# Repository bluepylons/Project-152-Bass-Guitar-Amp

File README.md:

This is a preamplifier circuit for a bass-amp, using much of [Rod Elliot's design](https://sound-au.com/project152-1.htm) over at Sound Au, with some changes:

* The EQ board is broken off into a separate board, so that the main preamp design could be used with different EQ schemes (graphic, etc.). 
* I skipped adding a compressor, though this can probably be added immediately after the EQ chain if needed.
* Added a headphone output

Since Chinese PCB fabrication is dramatically cheaper if your design is 100x100mm or smaller, this design is broken up into separate boards for the preamp, linear power supply (+/-12V), and EQ stages.

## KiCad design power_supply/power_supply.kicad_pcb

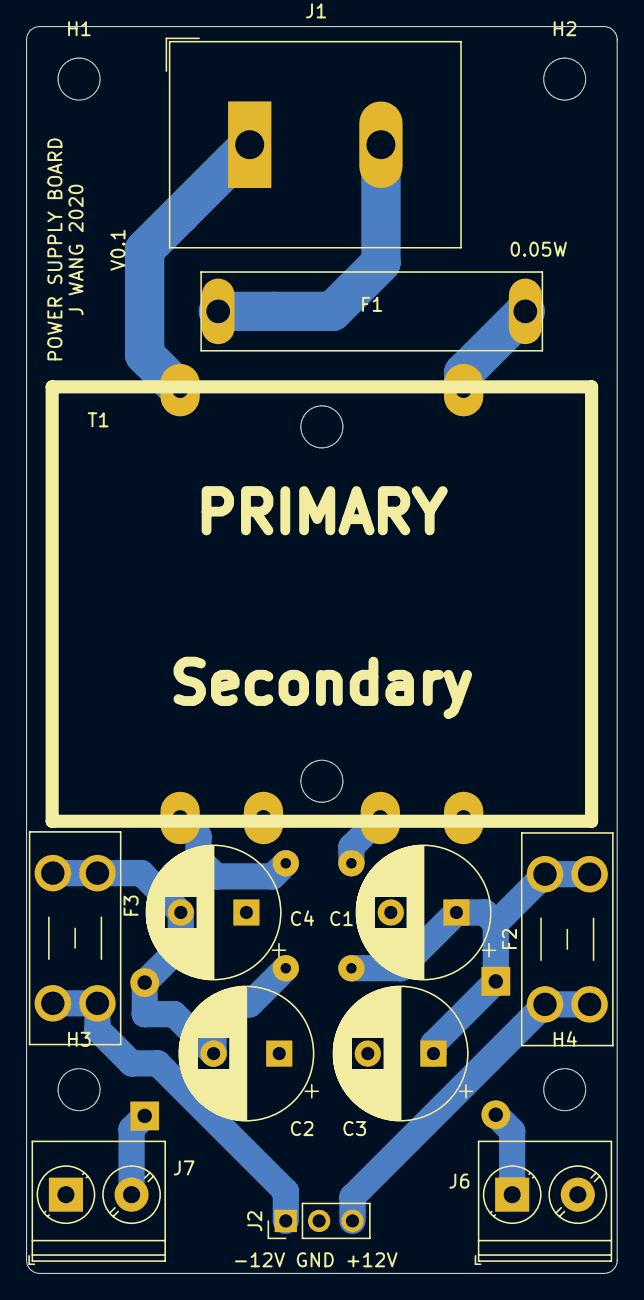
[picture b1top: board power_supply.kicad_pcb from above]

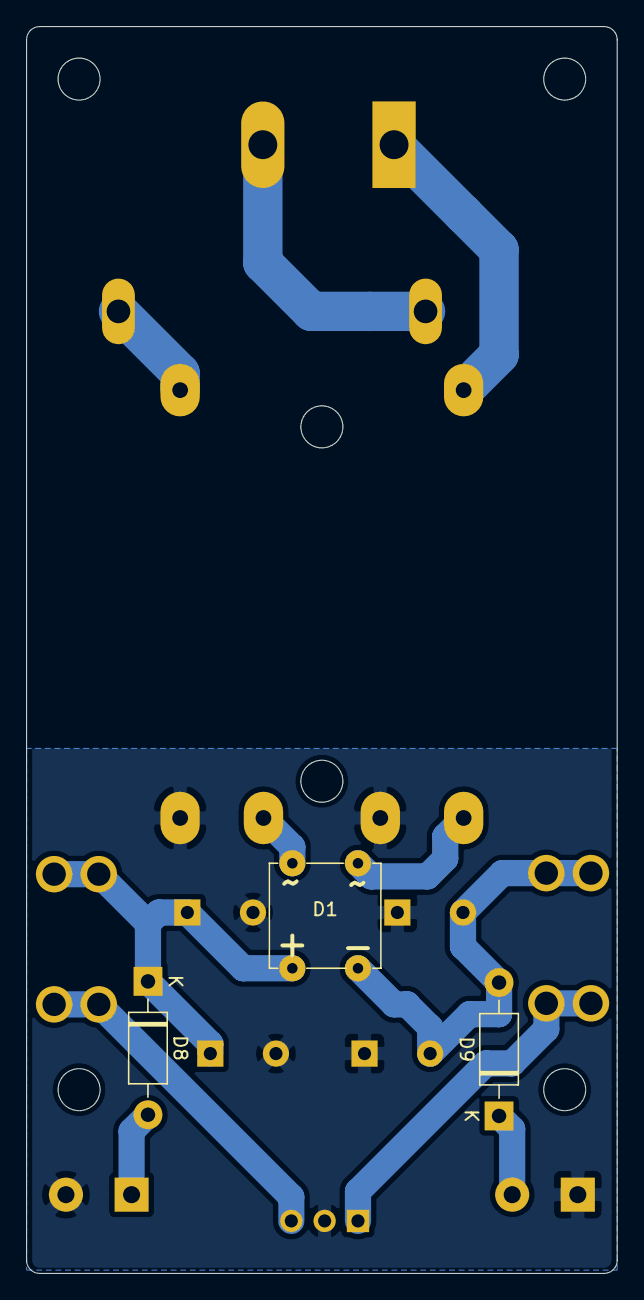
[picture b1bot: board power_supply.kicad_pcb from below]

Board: 2 copper layers, 45.0 x 95.0 mm, 19 parts (3 on the bottom side), 12 nets.

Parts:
C1, C2, C3, C4: 1000uF 35V; CP_Radial_D10.0mm_P5.00mm
D1: D_Bridge_+-AA; DiodesIncDF-M
D8, D9: 1N5819; D_DO-41_SOD81_P10.16mm_Horizontal
F1: Fuse; Keystone-3527-Fuseholder
F2, F3: Fuse; Fuseholder_Blade_Mini_Keystone_3568
H1, H2, H3, H4: MountingHole; MountingHole_3.2mm_M3_DIN965
J1: Conn_01x02_Female; TerminalBlock_Dinkle_DT-55-B01X-02_P10.00mm
J2: Conn_01x03_Male; PinHeader_1x03_P2.54mm_Vertical
J6, J7: Conn_01x02_Male; TerminalBlock_Phoenix_PT-1,5-2-5.0-H_1x02_P5.00mm_Horizontal
T1: Transformer_1P_2S; TE490080XXRC62

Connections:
+12V: C1.1, C3.1, D1.1, D8.1, F2.2
-12V: C2.2, C4.2, D1.2, D9.2, F3.2
GND: C1.2, C2.1, C3.2, C4.1, J2.2, J6.2, J7.1, T1.4, T1.5
unnamed: D1.3, T1.6
unnamed: D1.4, T1.3
unnamed: D8.2, J6.1
unnamed: D9.1, J7.2
unnamed: F1.1, T1.1
unnamed: F1.2, J1.2
unnamed: F2.1, J2.3
unnamed: F3.1, J2.1
unnamed: J1.1, T1.2

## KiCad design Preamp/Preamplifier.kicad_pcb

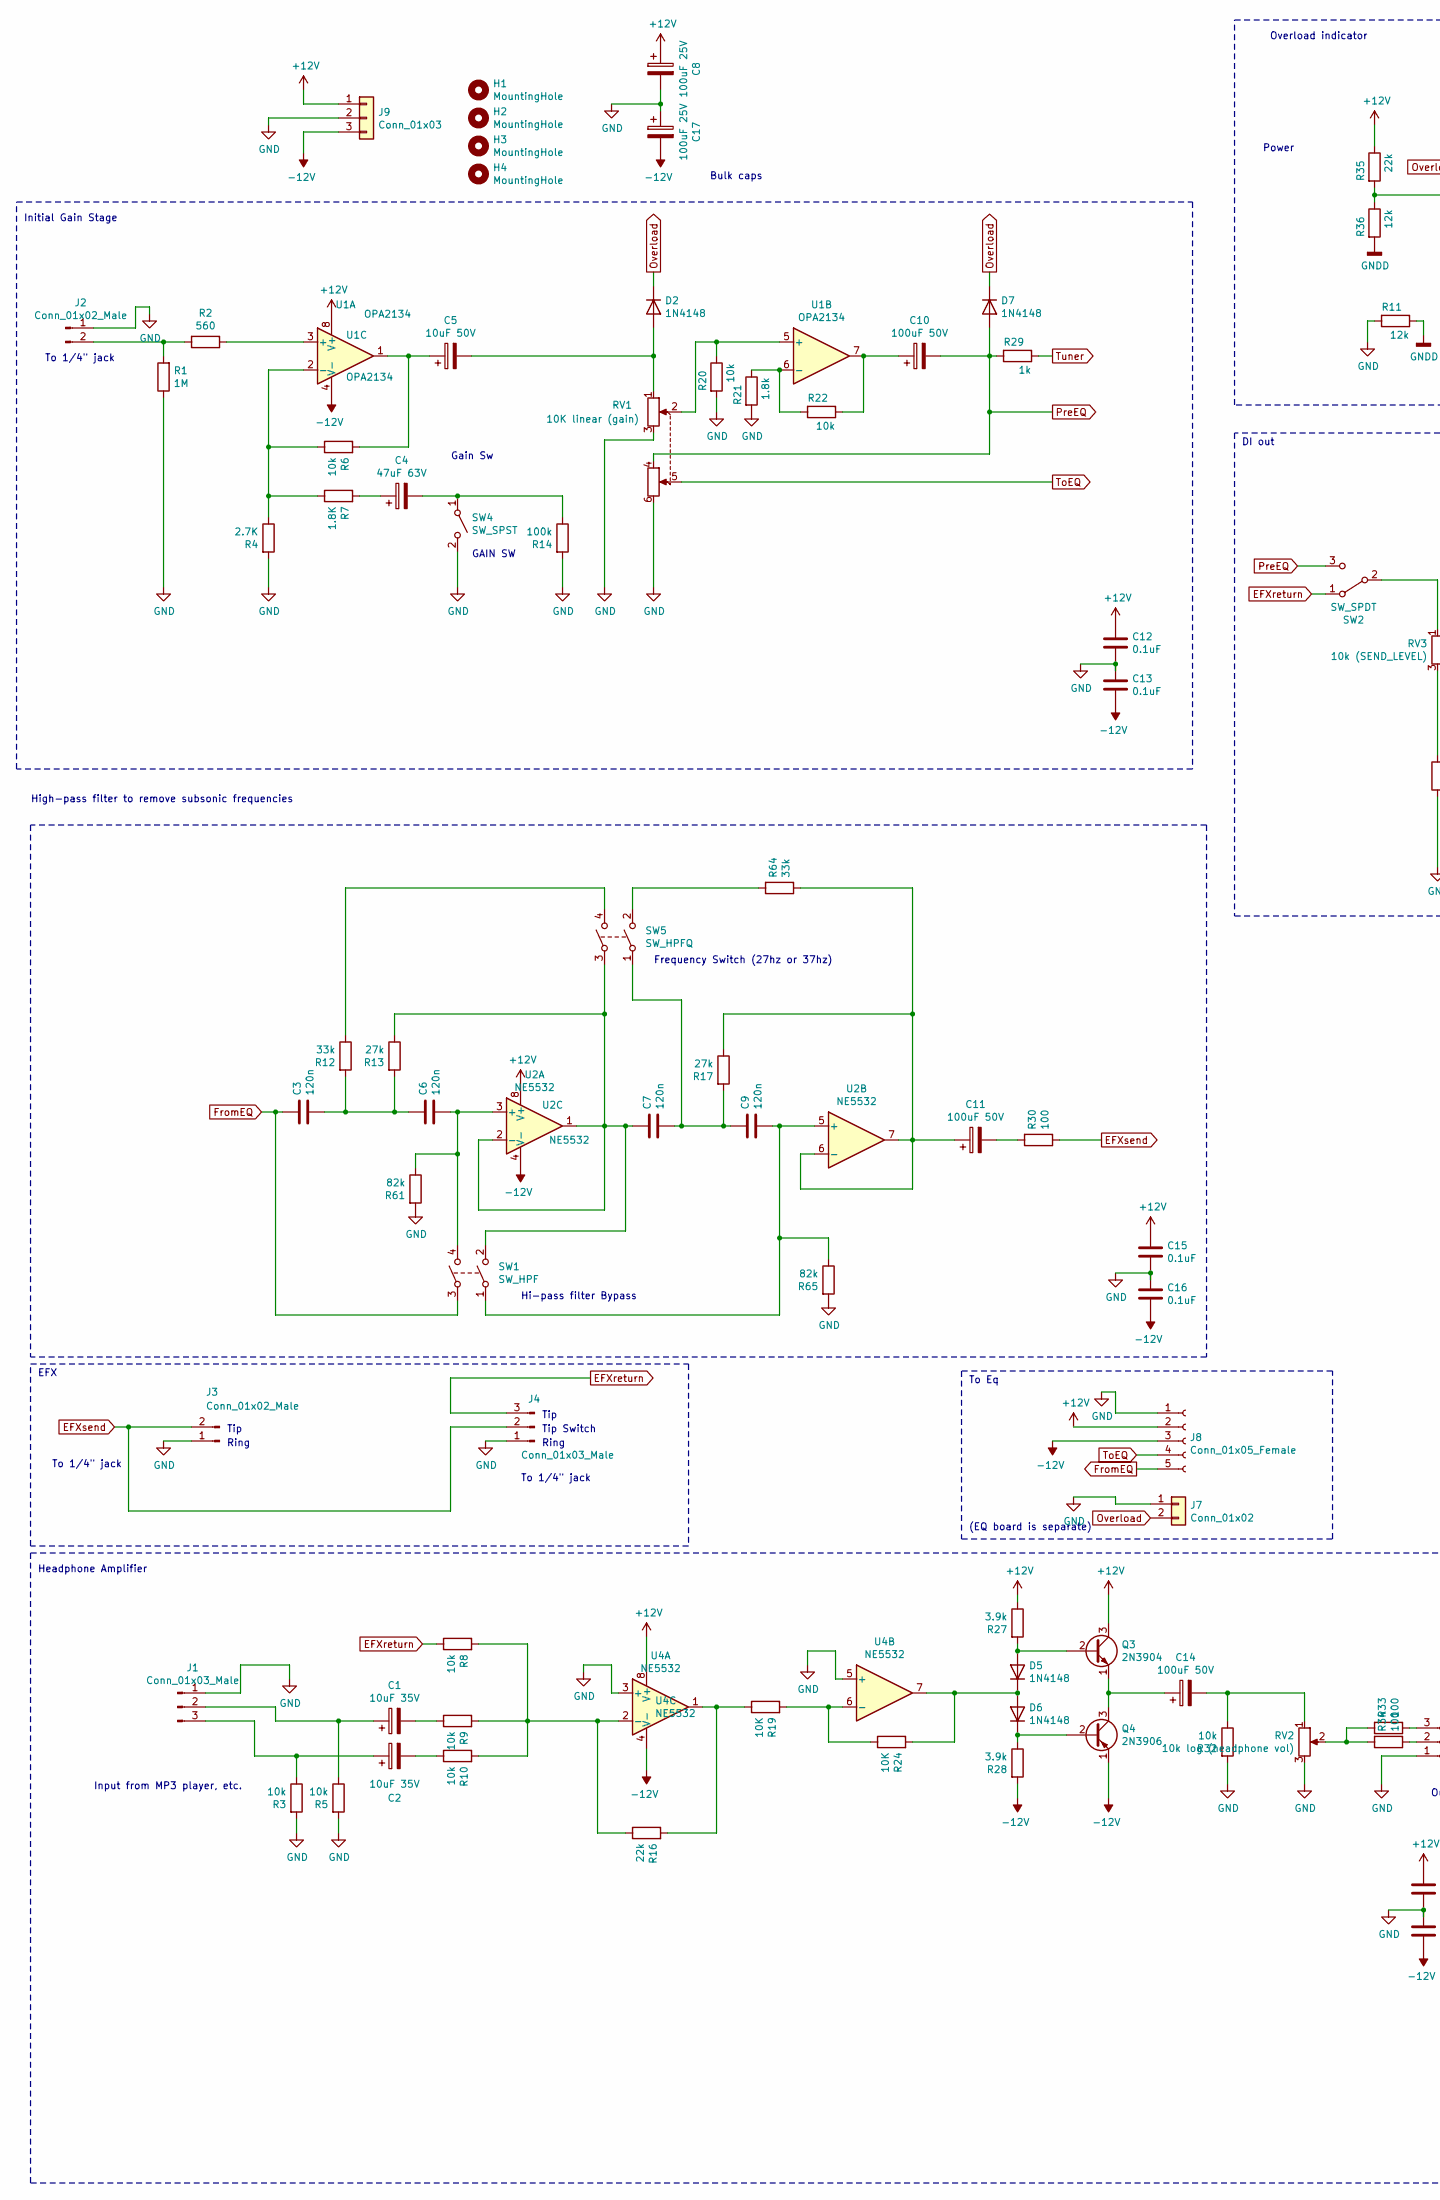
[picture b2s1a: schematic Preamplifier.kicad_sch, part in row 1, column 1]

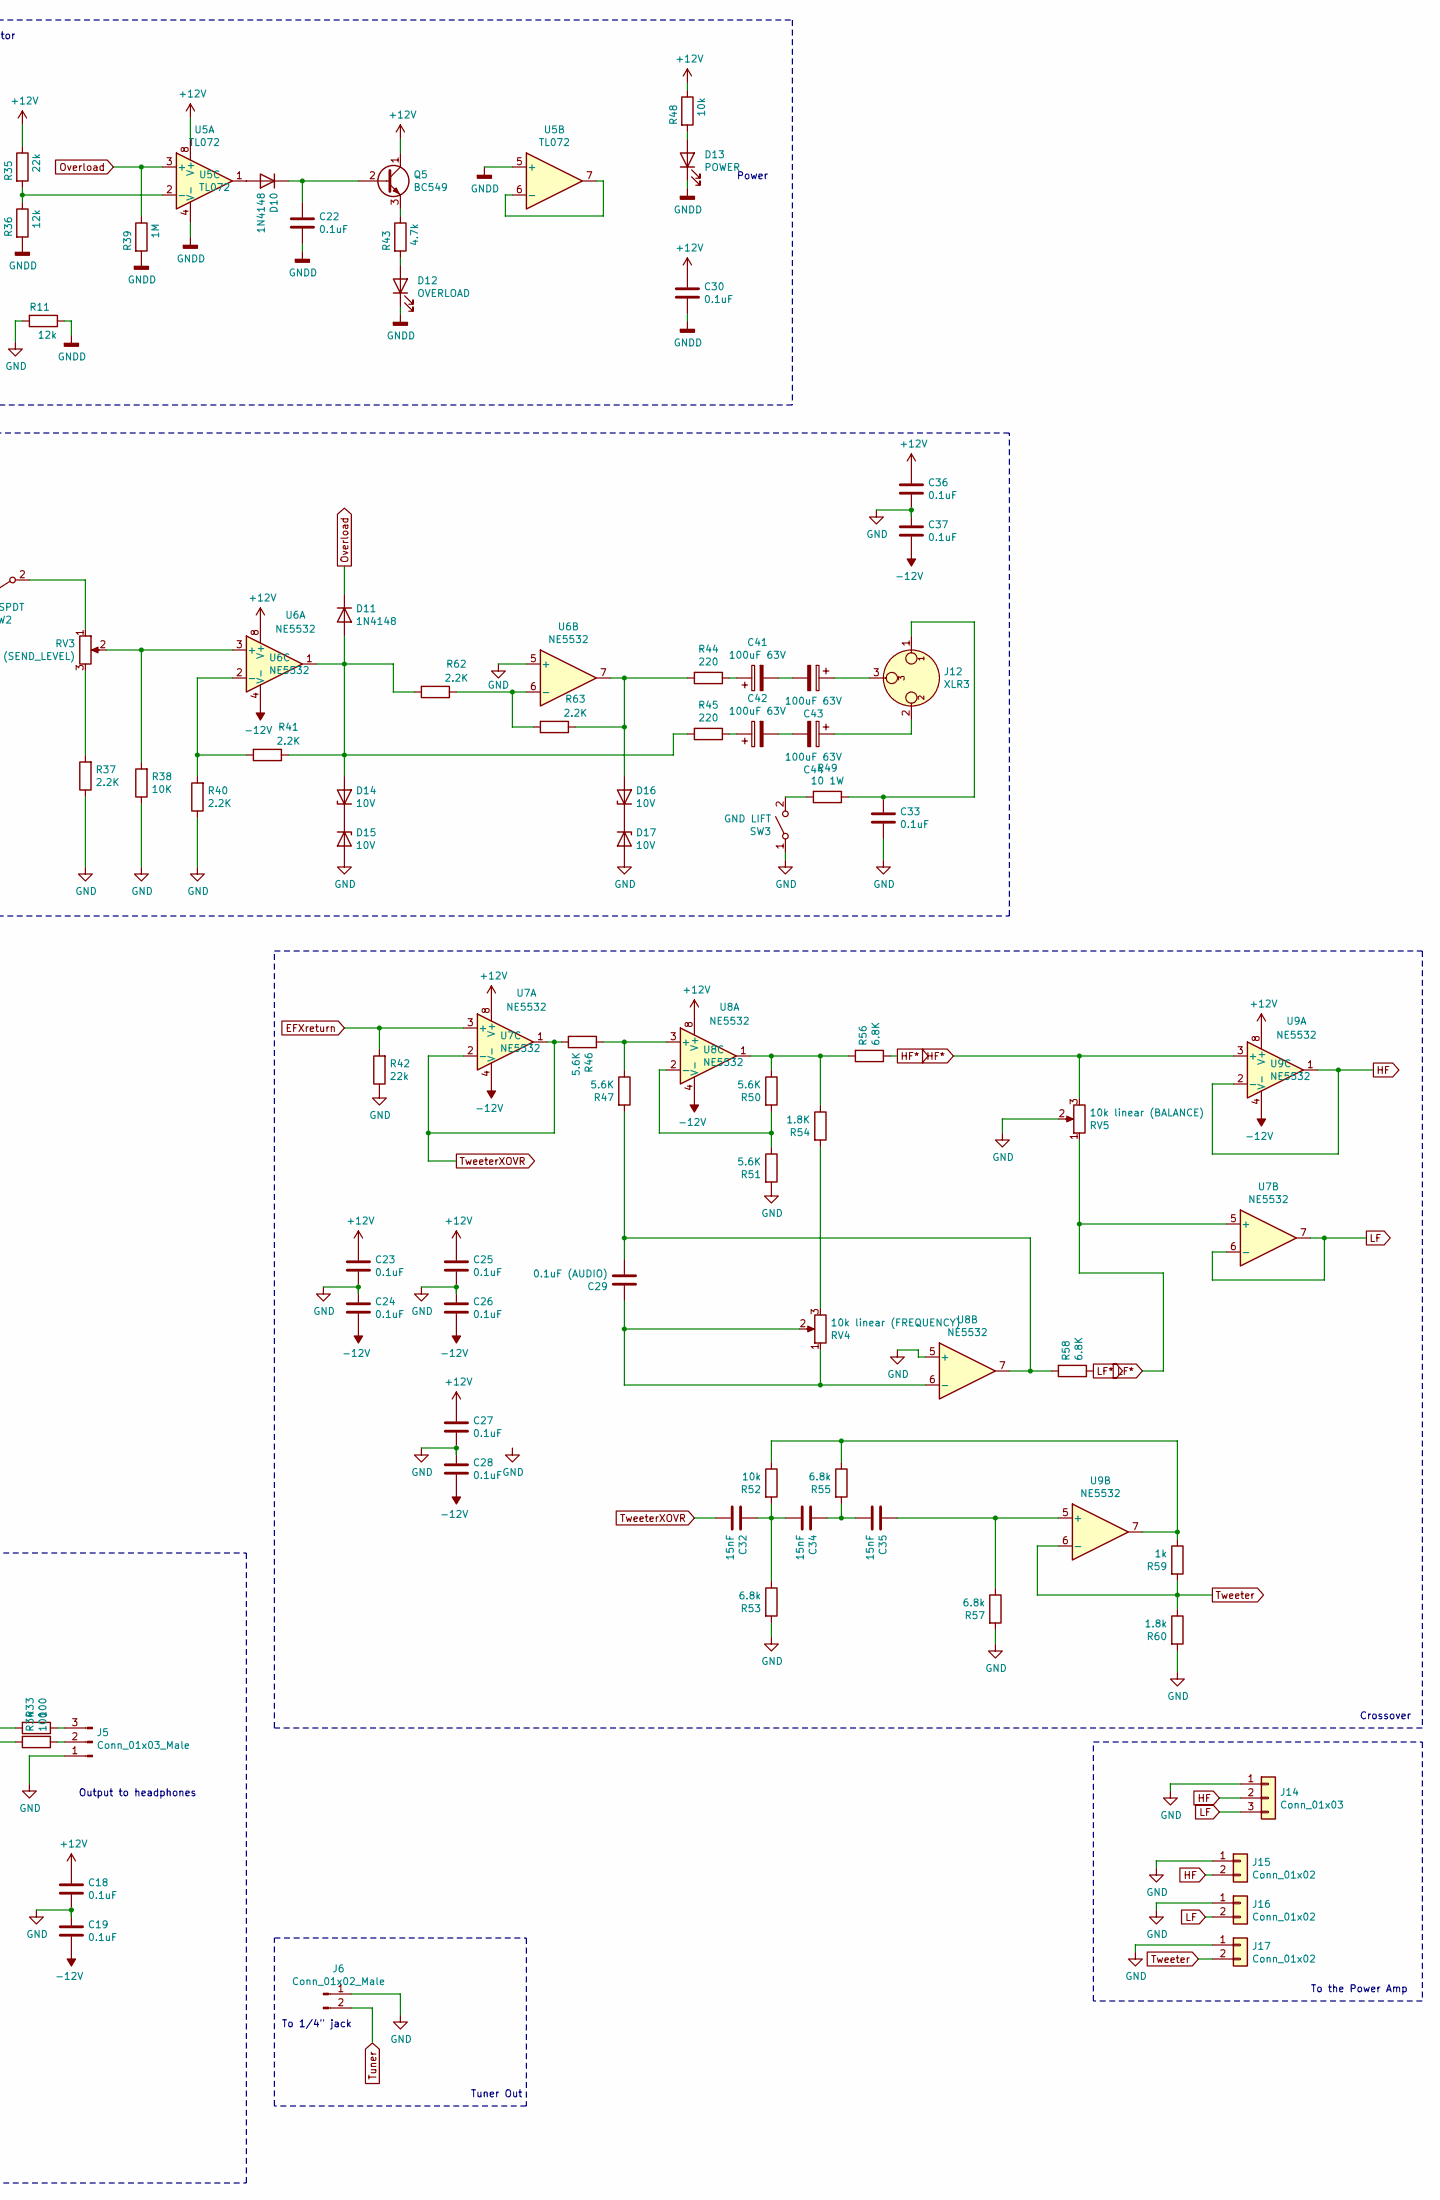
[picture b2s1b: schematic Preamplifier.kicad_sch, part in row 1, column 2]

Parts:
C1, C2: 10uF 35V; CP_Radial_D5.0mm_P2.00mm
C3, C6, C7, C9: 120n; C_Rect_L7.2mm_W3.5mm_P5.00mm_FKS2_FKP2_MKS2_MKP2
C4: 47uF 63V; CP_Radial_D8.0mm_P5.00mm
C5: 10uF 50V; CP_Radial_D6.3mm_P2.50mm
C8, C17: 100uF 25V; CP_Radial_D6.3mm_P2.50mm
C10, C11: 100uF 50V; CP_Radial_D8.0mm_P3.50mm
C12, C13, C15, C16, C18, C19, C22, C23, C24, C25, C26, C27, C28, C30, C33, C36, C37: 0.1uF; C_0805_2012Metric_Pad1.15x1.40mm_HandSolder
C14: 100uF 50V; CP_Radial_D8.0mm_P2.50mm
C29: 0.1uF (AUDIO); C_Rect_L7.2mm_W2.5mm_P5.00mm_FKS2_FKP2_MKS2_MKP2
C32, C34, C35: 15nF; C_Rect_L7.2mm_W2.5mm_P5.00mm_FKS2_FKP2_MKS2_MKP2
C41, C42, C43, C44: 100uF 63V; CP_Radial_D8.0mm_P3.50mm
D2, D5, D6: 1N4148; D_SOD-123
D7, D10, D11: 1N4148; D_DO-35_SOD27_P7.62mm_Horizontal
D12: OVERLOAD; LED_D3.0mm
D13: POWER; LED_D3.0mm
D14, D15, D16, D17: 10V; D_DO-41_SOD81_P7.62mm_Horizontal
H1, H2, H3, H4: MountingHole; MountingHole_3.2mm_M3_ISO7380
J1, J4, J5: Conn_01x03_Male; PinHeader_1x03_P2.54mm_Vertical
J2, J3, J6: Conn_01x02_Male; PinHeader_1x02_P2.54mm_Vertical
J7, J15, J16, J17: Conn_01x02; PinHeader_1x02_P2.54mm_Vertical
J8: Conn_01x05_Female; PinHeader_1x05_P2.54mm_Vertical
J9, J14: Conn_01x03; PinHeader_1x03_P2.54mm_Vertical
J12: XLR3; PinHeader_1x03_P2.54mm_Vertical
Q3: 2N3904; TO-92_Inline
Q4: 2N3906; TO-92_Inline
Q5: BC549; TO-92_Inline
R1, R39: 1M; R_0805_2012Metric_Pad1.15x1.40mm_HandSolder
R2: 560; R_0805_2012Metric_Pad1.15x1.40mm_HandSolder
R3, R5, R6, R8, R9, R10, R20, R22, R32, R48, R52: 10k; R_0805_2012Metric_Pad1.15x1.40mm_HandSolder
R4: 2.7K; R_0805_2012Metric_Pad1.15x1.40mm_HandSolder
R7, R54: 1.8K; R_0805_2012Metric_Pad1.15x1.40mm_HandSolder
R11, R36: 12k; R_0805_2012Metric_Pad1.15x1.40mm_HandSolder
R12, R64: 33k; R_0805_2012Metric_Pad1.15x1.40mm_HandSolder
R13, R17: 27k; R_0805_2012Metric_Pad1.15x1.40mm_HandSolder
R14: 100k; R_0805_2012Metric_Pad1.15x1.40mm_HandSolder
R16, R35, R42: 22k; R_0805_2012Metric_Pad1.15x1.40mm_HandSolder
R19, R24, R38: 10K; R_0805_2012Metric_Pad1.15x1.40mm_HandSolder
R21, R60: 1.8k; R_0805_2012Metric_Pad1.15x1.40mm_HandSolder
R27, R28: 3.9k; R_0805_2012Metric_Pad1.15x1.40mm_HandSolder
R29, R59: 1k; R_0805_2012Metric_Pad1.15x1.40mm_HandSolder
R30, R33, R34: 100; R_1206_3216Metric_Pad1.42x1.75mm_HandSolder
R37, R40, R41, R62, R63: 2.2K; R_0805_2012Metric_Pad1.15x1.40mm_HandSolder
R43: 4.7k; R_0805_2012Metric_Pad1.15x1.40mm_HandSolder
R44, R45: 220; R_1206_3216Metric_Pad1.42x1.75mm_HandSolder
R46, R47, R50, R51: 5.6K; R_0805_2012Metric_Pad1.15x1.40mm_HandSolder
R49: 10 1W; R_Axial_DIN0411_L9.9mm_D3.6mm_P12.70mm_Horizontal
R53, R55, R57: 6.8k; R_0805_2012Metric_Pad1.15x1.40mm_HandSolder
R56, R58: 6.8K; R_0805_2012Metric_Pad1.15x1.40mm_HandSolder
R61, R65: 82k; R_0805_2012Metric_Pad1.15x1.40mm_HandSolder
RV1: 10K linear (gain); PinHeader_1x06_P2.54mm_Vertical
RV2: 10k log (headphone vol); PinHeader_1x03_P2.54mm_Vertical
RV3: 10k (SEND_LEVEL); PinHeader_1x03_P2.54mm_Vertical
RV4: 10k linear (FREQUENCY); RM-065-TRIMPOT
RV5: 10k linear (BALANCE); RM-065-TRIMPOT
SW1: SW_HPF; PinHeader_2x02_P2.54mm_Vertical
SW2: SW_SPDT; PinHeader_1x03_P2.54mm_Vertical
SW3: GND LIFT; PinHeader_1x02_P2.54mm_Vertical
SW4: SW_SPST; PinHeader_1x02_P2.54mm_Vertical
SW5: SW_HPFQ; PinHeader_2x02_P2.54mm_Vertical
U1: OPA2134; DIP-8_W7.62mm_Socket
U2, U4, U6, U7, U8, U9: NE5532; DIP-8_W7.62mm_Socket
U5: TL072; DIP-8_W7.62mm_Socket

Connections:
+12V: C8.1, C12.2, C15.2, C18.2, C23.2, C25.2, C27.2, C30.2, C36.2, J8.2, J9.1, Q3.3 (C), Q5.1 (C), R27.1, R35.1, R48.1, U1.8 (V+), U2.8 (V+), U4.8 (V+), U5.8 (V+), U6.8 (V+), U7.8 (V+), U8.8 (V+), U9.8 (V+)
-12V: C13.1, C16.1, C17.2, C19.1, C24.1, C26.1, C28.1, C37.1, J8.3, J9.3, Q4.1 (E), R28.2, U1.4 (V-), U2.4 (V-), U4.4 (V-), U6.4 (V-), U7.4 (V-), U8.4 (V-), U9.4 (V-)
EFXreturn: J4.3, R8.1, R42.2, SW2.1 (A), U7.3 (+)
EFXsend: J3.2, J4.2, R30.1
FromEQ: C3.2, J8.5, SW1.3
GND: C8.2, C12.1, C13.2, C15.1, C16.2, C17.1, C18.1, C19.2, C23.1, C24.2, C25.1, C26.2, C27.1, C28.2, C33.1, C36.1, C37.2, D15.2 (A), D17.2 (A), J1.1, J2.1, J3.1, J4.1, J5.1, J6.1, J7.1, J8.1, J9.2, J14.1, J15.1, J16.1, J17.1, R1.1, R3.2, R4.2, R5.2, R11.2, R14.2, R20.2, R21.2, R32.2, R37.1, R38.1, R40.1, R42.1, R51.2, R53.2, R57.2, R60.2, R61.2, R65.2, RV1.3, RV1.6, RV2.3, RV5.2, SW3.1 (A), SW4.2 (B), U4.3 (+), U4.5 (+), U6.5 (+), U8.5 (+)
GNDD: C22.1, C30.1, D12.1 (K), D13.1 (K), R11.1, R36.2, R39.2, U5.4 (V-), U5.5 (+)
HF: J14.2, J15.2, U9.1, U9.2 (-)
HF*: R56.1, RV5.3, U9.3 (+)
LF: J14.3, J16.2, U7.6 (-), U7.7
LF*: R58.1, RV5.1, U7.5 (+)
unnamed: C1.1, J1.2, R5.1
unnamed: C1.2, R9.1
unnamed: C2.1, J1.3, R3.1
unnamed: C2.2, R10.1
unnamed: C3.1, C6.2, R12.2, R13.2
unnamed: C4.1, R7.2
unnamed: C4.2, R14.1, SW4.1 (A)
unnamed: C5.1, R6.2, U1.1
unnamed: C5.2, D2.2 (A), RV1.1
unnamed: C6.1, R61.1, SW1.4, U2.3 (+)
unnamed: C7.1, C9.2, R17.2, SW5.1
unnamed: C7.2, R13.1, SW1.2, SW5.3, U2.1, U2.2 (-)
unnamed: C9.1, R65.1, SW1.1, U2.5 (+)
unnamed: C10.1, R22.1, U1.7
unnamed: C11.1, R17.1, R64.1, U2.6 (-), U2.7
unnamed: C11.2, R30.2
unnamed: C14.1, Q3.1 (E), Q4.3 (C)
unnamed: C14.2, R32.1, RV2.1
unnamed: C22.2, D10.1 (K), Q5.2 (B)
unnamed: C29.1, R47.2, R58.2, U8.7
unnamed: C29.2, RV4.1, RV4.2, U8.6 (-)
unnamed: C32.2, C34.1, R52.2, R53.1
unnamed: C33.2, J12.1, R49.1
unnamed: C34.2, C35.1, R55.2
unnamed: C35.2, R57.1, U9.5 (+)
unnamed: C41.1, R44.1
unnamed: C41.2, C43.2
unnamed: C42.1, R45.1
unnamed: C42.2, C44.2
unnamed: C43.1, J12.3
unnamed: C44.1, J12.2
unnamed: D5.1 (K), D6.2 (A), R24.2, U4.7
unnamed: D5.2 (A), Q3.2 (B), R27.2
unnamed: D6.1 (K), Q4.2 (B), R28.1
unnamed: D10.2 (A), U5.1
unnamed: D11.2 (A), D14.2 (A), R41.1, R45.2, R62.2, U6.1
unnamed: D12.2 (A), R43.2
unnamed: D13.2 (A), R48.2
unnamed: D14.1 (K), D15.1 (K)
unnamed: D16.1 (K), D17.1 (K)
unnamed: D16.2 (A), R44.2, R63.1, U6.7
unnamed: J2.2, R1.2, R2.2
unnamed: J5.2, R34.1
unnamed: J5.3, R33.1
unnamed: Q5.3 (E), R43.1
unnamed: R2.1, U1.3 (+)
unnamed: R4.1, R6.1, R7.1, U1.2 (-)
unnamed: R8.2, R9.2, R10.2, R16.1, U4.2 (-)
unnamed: R12.1, SW5.4
unnamed: R16.2, R19.1, U4.1
unnamed: R19.2, R24.1, U4.6 (-)
unnamed: R20.1, RV1.2, U1.5 (+)
unnamed: R21.1, R22.2, U1.6 (-)
unnamed: R33.2, R34.2, RV2.2
unnamed: R35.2, R36.1, U5.2 (-)
unnamed: R37.2, RV3.3
unnamed: R38.2, RV3.2, U6.3 (+)
unnamed: R40.2, R41.2, U6.2 (-)
unnamed: R46.2, R47.1, U8.3 (+)
unnamed: R49.2, SW3.2 (B)
unnamed: R50.1, R54.1, R56.2, U8.1
unnamed: R50.2, R51.1, U8.2 (-)
unnamed: R52.1, R55.1, R59.1, U9.7
unnamed: R54.2, RV4.3
unnamed: R62.1, R63.2, U6.6 (-)
unnamed: R64.2, SW5.2
unnamed: RV3.1, SW2.2 (B)
unnamed: U5.6 (-), U5.7
Overload: D2.1 (K), D7.1 (K), D11.1 (K), J7.2, R39.1, U5.3 (+)
PreEQ: C10.2, D7.2 (A), R29.2, RV1.4, SW2.3 (C)
ToEQ: J8.4, RV1.5
Tuner: J6.2, R29.1
Tweeter: J17.2, R59.2, R60.1, U9.6 (-)
TweeterXOVR: C32.1, R46.1, U7.1, U7.2 (-)

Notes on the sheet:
Initial Gain Stage
High-pass filter to remove subsonic frequencies
EFX
Headphone Amplifier
To 1/4" jack
Input from MP3 player, etc.
Tip
Ring
Gain Sw
GAIN SW
Hi-pass filter Bypass
Tip Switch
Frequency Switch (27hz or 37hz)
Bulk caps
To Eq
(EQ board is separate)
DI out
Power
Overload indicator
Output to headphones
Tuner Out
To the Power Amp
Crossover

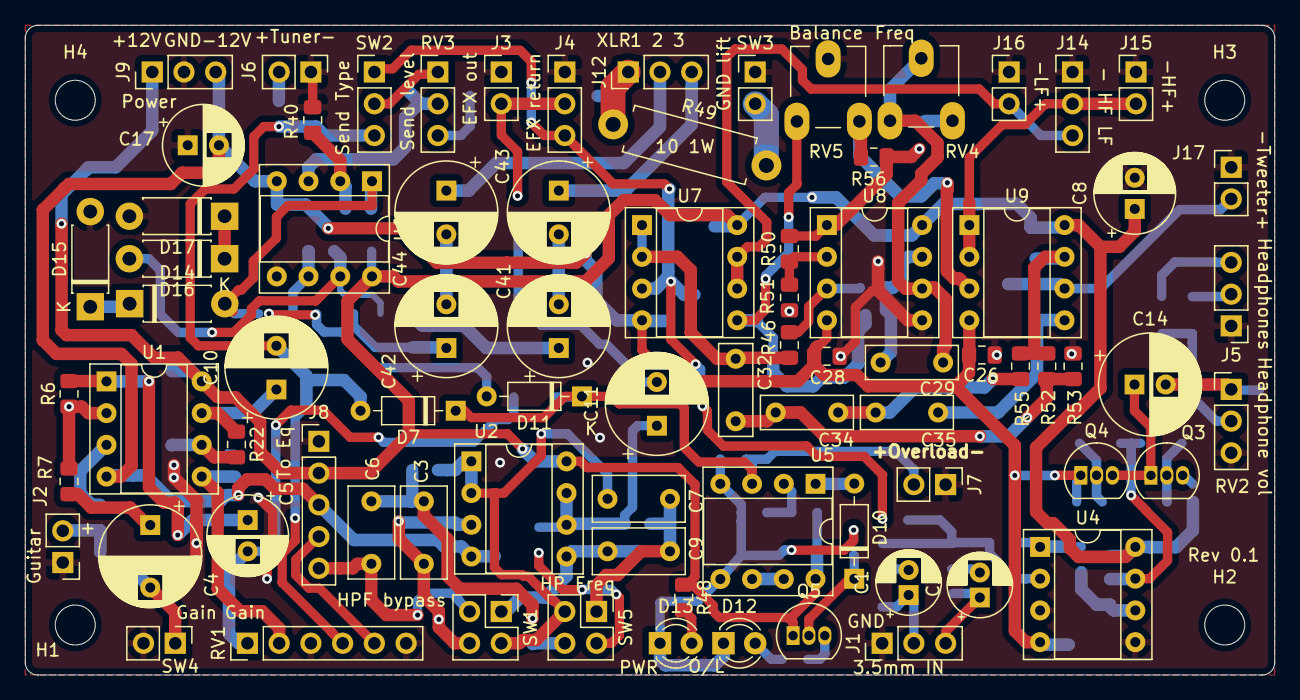
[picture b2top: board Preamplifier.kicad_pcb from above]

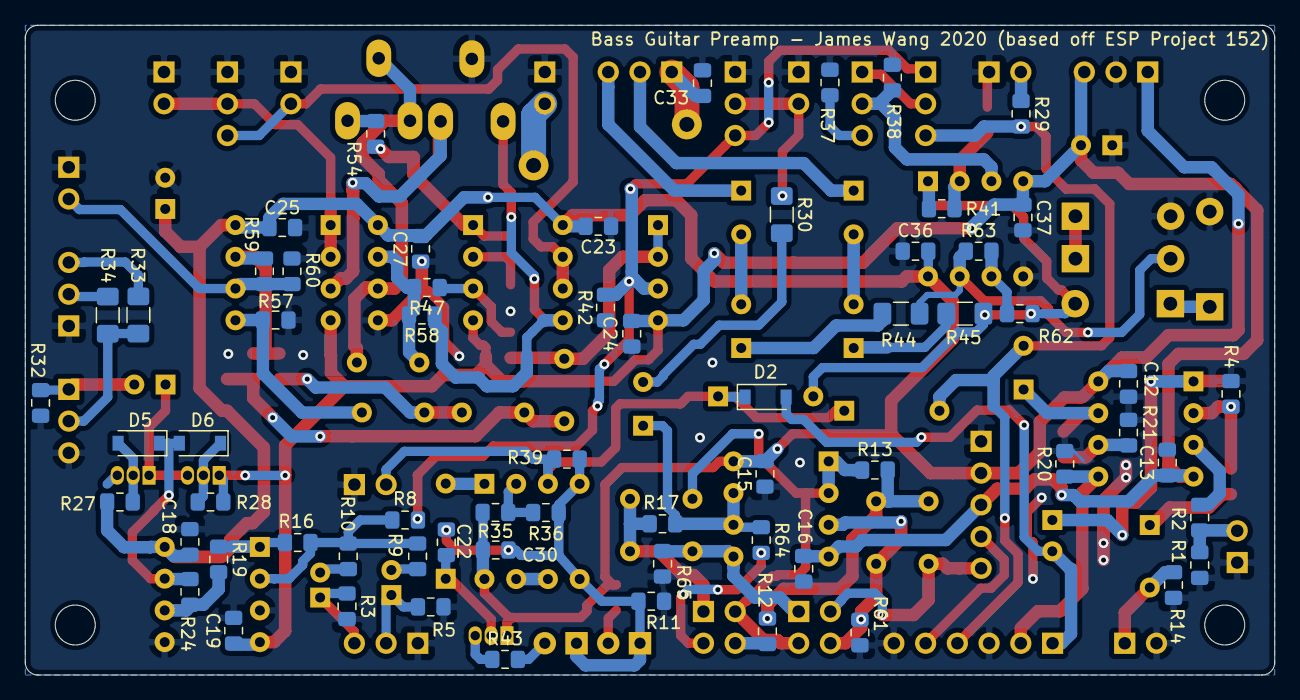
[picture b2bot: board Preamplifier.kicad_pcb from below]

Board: 2 copper layers, 100.0 x 52.0 mm, 148 parts (64 on the bottom side), 85 nets.

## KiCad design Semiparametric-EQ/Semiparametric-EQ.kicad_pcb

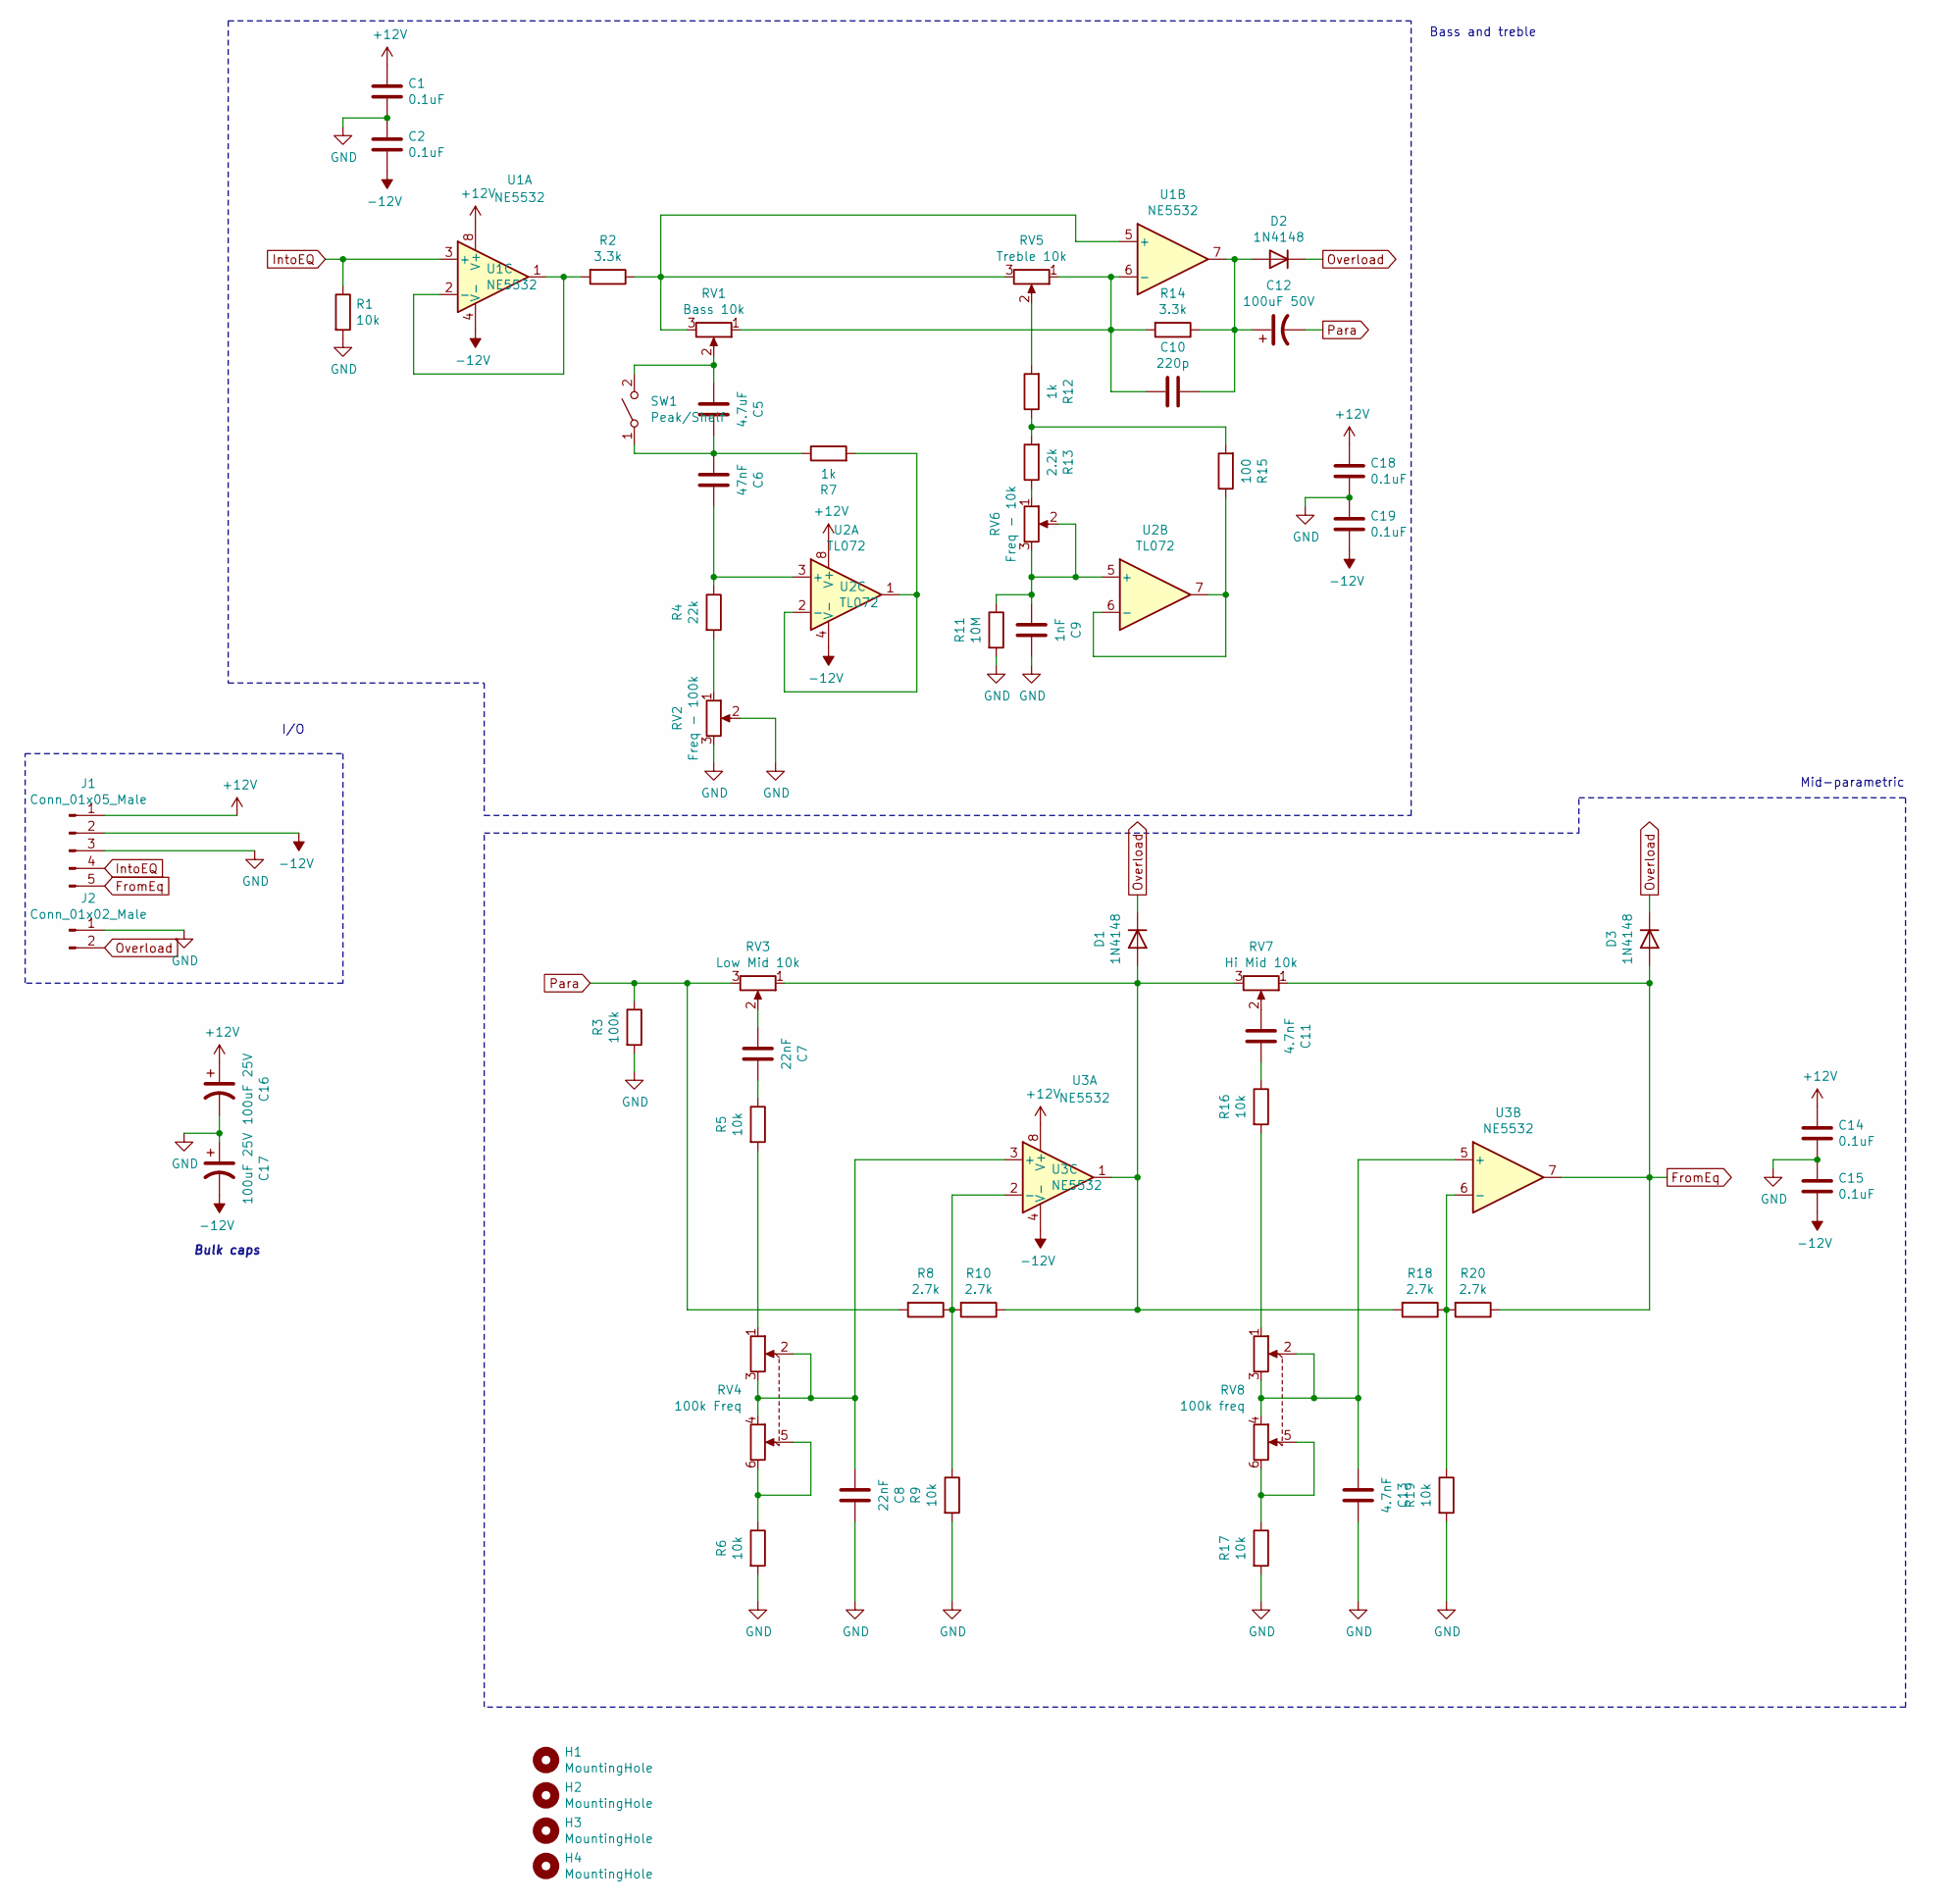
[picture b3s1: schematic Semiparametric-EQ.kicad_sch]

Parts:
C1, C2, C14, C15, C18, C19: 0.1uF; C_0805_2012Metric_Pad1.15x1.40mm_HandSolder
C5: 4.7uF; C_Rect_L7.2mm_W8.5mm_P5.00mm_FKP2_FKP2_MKS2_MKP2
C6: 47nF; C_0805_2012Metric_Pad1.15x1.40mm_HandSolder
C7, C8: 22nF; C_0805_2012Metric_Pad1.15x1.40mm_HandSolder
C9: 1nF; C_0805_2012Metric_Pad1.15x1.40mm_HandSolder
C10: 220p; C_0805_2012Metric_Pad1.15x1.40mm_HandSolder
C11, C13: 4.7nF; C_0805_2012Metric_Pad1.15x1.40mm_HandSolder
C12: 100uF 50V; CP_Radial_D8.0mm_P3.50mm
C16, C17: 100uF 25V; CP_Radial_D6.3mm_P2.50mm
D1, D2, D3: 1N4148; D_SOD-123
H1, H2, H3, H4: MountingHole; MountingHole_3.2mm_M3_ISO7380
J1: Conn_01x05_Male; PinHeader_1x05_P2.54mm_Vertical
J2: Conn_01x02_Male; PinHeader_1x02_P2.54mm_Vertical
R1, R5, R6, R9, R16, R17, R19: 10k; R_0805_2012Metric_Pad1.15x1.40mm_HandSolder
R2, R14: 3.3k; R_0805_2012Metric_Pad1.15x1.40mm_HandSolder
R3: 100k; R_0805_2012Metric_Pad1.15x1.40mm_HandSolder
R4: 22k; R_0805_2012Metric_Pad1.15x1.40mm_HandSolder
R7, R12: 1k; R_0805_2012Metric_Pad1.15x1.40mm_HandSolder
R8, R10, R18, R20: 2.7k; R_0805_2012Metric_Pad1.15x1.40mm_HandSolder
R11: 10M; R_0805_2012Metric_Pad1.15x1.40mm_HandSolder
R13: 2.2k; R_0805_2012Metric_Pad1.15x1.40mm_HandSolder
R15: 100; R_0805_2012Metric_Pad1.15x1.40mm_HandSolder
RV1: Bass 10k; PinHeader_1x03_P2.54mm_Vertical
RV2: Freq - 100k; PinHeader_1x03_P2.54mm_Vertical
RV3: Low Mid 10k; PinHeader_1x03_P2.54mm_Vertical
RV4: 100k Freq; PinHeader_1x06_P2.54mm_Vertical
RV5: Treble 10k; PinHeader_1x03_P2.54mm_Vertical
RV6: Freq - 10k; PinHeader_1x03_P2.54mm_Vertical
RV7: Hi Mid 10k; PinHeader_1x03_P2.54mm_Vertical
RV8: 100k freq; PinHeader_1x06_P2.54mm_Vertical
SW1: Peak/Shelf; PinHeader_1x02_P2.54mm_Vertical
U1, U3: NE5532; DIP-8_W7.62mm_Socket
U2: TL072; DIP-8_W7.62mm_Socket

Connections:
+12V: C1.1, C14.1, C16.1, C18.1, J1.1, U1.8 (V+), U2.8 (V+), U3.8 (V+)
-12V: C2.2, C15.2, C17.2, C19.2, J1.2, U1.4 (V-), U2.4 (V-), U3.4 (V-)
FromEq: D3.2 (A), J1.5, R20.1, RV7.1, U3.7
GND: C1.2, C2.1, C8.1, C9.1, C13.1, C14.2, C15.1, C16.2, C17.1, C18.2, C19.1, J1.3, J2.1, R1.2, R3.2, R6.2, R9.2, R11.2, R17.2, R19.2, RV2.2, RV2.3
IntoEQ: J1.4, R1.1, U1.3 (+)
unnamed: C5.1, C6.2, R7.1, SW1.1 (A)
unnamed: C5.2, RV1.2, SW1.2 (B)
unnamed: C6.1, R4.1, U2.3 (+)
unnamed: C7.1, R5.1
unnamed: C7.2, RV3.2
unnamed: C8.2, RV4.2, RV4.3, RV4.4, U3.3 (+)
unnamed: C9.2, R11.1, RV6.2, RV6.3, U2.5 (+)
unnamed: C10.1, C12.1, D2.2 (A), R14.1, U1.7
unnamed: C10.2, R14.2, RV1.1, RV5.1, U1.6 (-)
unnamed: C11.1, R16.1
unnamed: C11.2, RV7.2
unnamed: C13.2, RV8.2, RV8.3, RV8.4, U3.5 (+)
unnamed: D1.2 (A), R10.1, R18.2, RV3.1, RV7.3, U3.1
unnamed: R2.1, RV1.3, RV5.3, U1.5 (+)
unnamed: R2.2, U1.1, U1.2 (-)
unnamed: R4.2, RV2.1
unnamed: R5.2, RV4.1
unnamed: R6.1, RV4.5, RV4.6
unnamed: R7.2, U2.1, U2.2 (-)
unnamed: R8.1, R9.1, R10.2, U3.2 (-)
unnamed: R12.1, R13.2, R15.2
unnamed: R12.2, RV5.2
unnamed: R13.1, RV6.1
unnamed: R15.1, U2.6 (-), U2.7
unnamed: R16.2, RV8.1
unnamed: R17.1, RV8.5, RV8.6
unnamed: R18.1, R19.1, R20.2, U3.6 (-)
Overload: D1.1 (K), D2.1 (K), D3.1 (K), J2.2
Para: C12.2, R3.1, R8.2, RV3.3

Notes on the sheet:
Bulk caps
I/O
Bass and treble
Mid-parametric

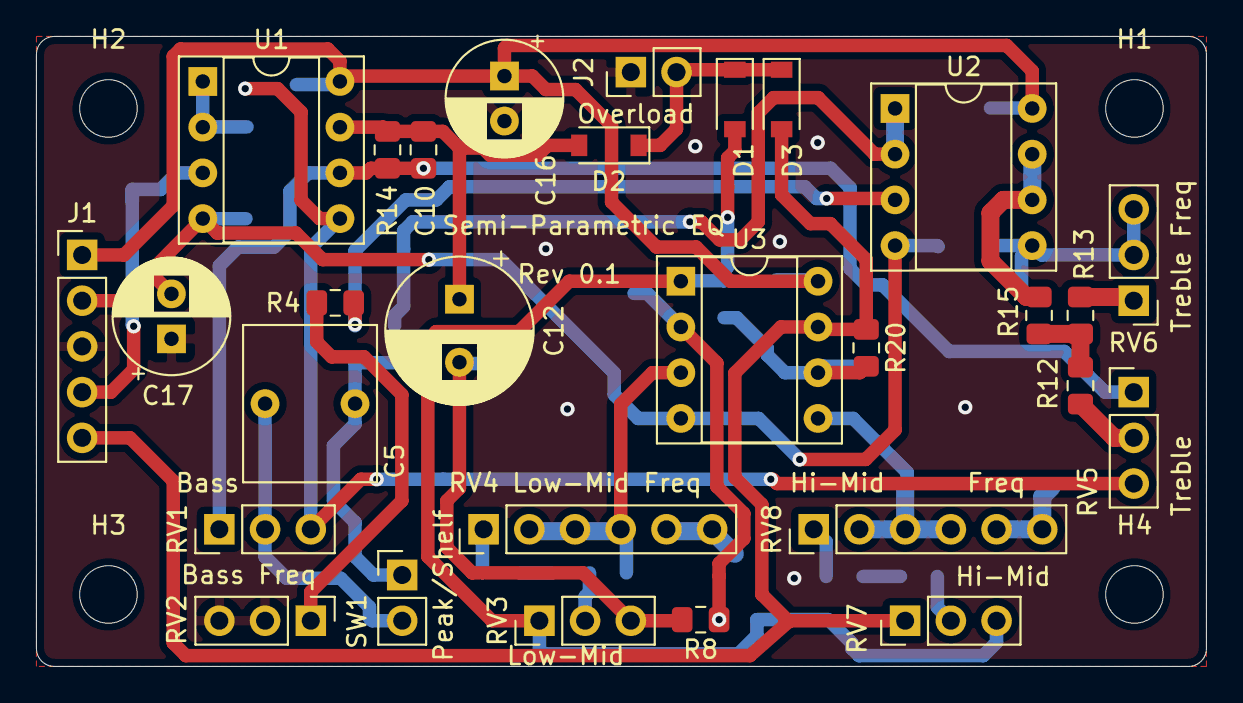
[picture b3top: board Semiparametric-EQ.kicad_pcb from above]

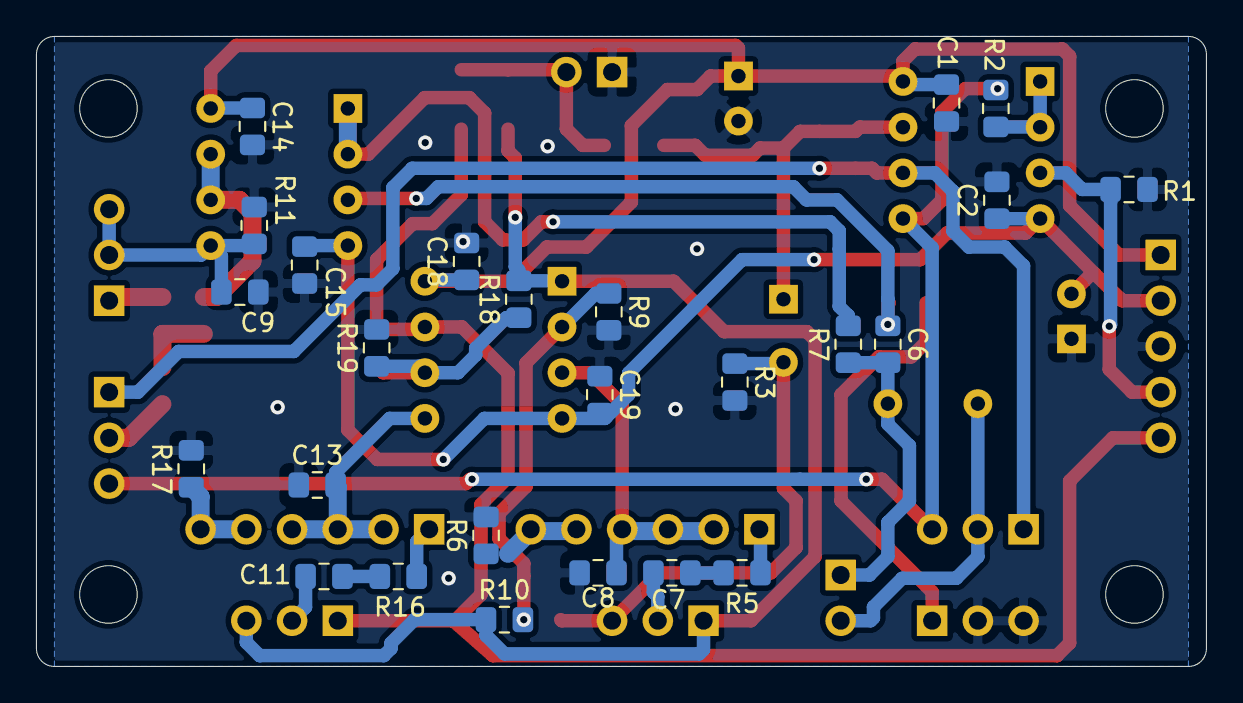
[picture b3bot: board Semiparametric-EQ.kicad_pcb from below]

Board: 2 copper layers, 65.0 x 35.0 mm, 58 parts (25 on the bottom side), 34 nets.

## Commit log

2019-12-24 :tada: Added .gitattributes & .gitignore files
2019-12-29 Did more work on amplifier
2020-01-09 Moved power supply off the main board
2020-01-19 Moved power supply off preamp
2020-01-20 Did some layout
2020-01-21 More layout work
    Also fixed some minor issues on the schematic
2020-01-22 More layout progress
2020-01-27 Did more layout work
2020-01-28 More layout work
2020-02-01 Moar layout
2020-02-05 More layout
2020-02-15 More layout work
    Still need to lay out the headphone amplifier.
2020-02-15 Removed re
2020-02-17 Finished first pass at layout.
    Still need to clean up silkscreen.
2020-02-17 Cleaned up silk screen + made Gerbers
2020-02-17 Added overload connector for EQ
2020-02-18 Added bulk caps, started eq board layout
2020-02-18 More layout work on the EQ unit
2020-02-19 More layout on EQ
2020-02-20 Finished first pass at Eq board
2020-02-23 Added top-side ground plane, started power supply work
2020-02-27 Finished power supply layout, sent out for first rev of boards
2020-06-11 Added text document listing panel connections
